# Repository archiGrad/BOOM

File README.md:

# BOOM
boom project with wannes. sensor implementatie
## includes
1: test blinkercode for 32 wroom with, but power supply is not going tgrough microusb, but through the board.  this is so we can connect the board safely to ther terminal block. in the following example i connect the VCC and GND from a 5v convertedr inbto the VIN pin and ibn tot GND pin of the nmicrocontroller though a breadboard.

<div style="display: flex; flex-wrap: wrap;">

</div>

2: screw terminal breakoput board for esp32. kiCad diagram and schamatics.
    download symbol from snapeda: https://www.snapeda.com/parts/ESP32-DEVKIT-V1/Do%20it/view-part/?t=esp32%20devkitv1

# Board Schematics
[View Schematics PDF](./media/fuse_box_schematic.pdf)

# design:
design iterations are documented here

<div style="display: flex; flex-wrap:wrap">

</div>
# partslist

https://www.automation24.be/nl/
<div style="display: flex; flex-wrap:wrap">

</div>

https://www.tinytronics.nl/

<div style="display: flex; flex-wrap:wrap">

</div>

# progressphotos
## visit 1

<div style="display: flex; flex-wrap:wrap">

</div>

### drone footage

<div style="display: flex; flex-wrap:wrap">

</div>

### print pics

<div style="display: flex; flex-wrap:wrap">

</div>

# Communication

<details>
<summary>  bespreking 1</summary>
veel kiezels, knmikkers in basin voor insecten
volgebadplaats wel 2 cm diepte nodig

oppervlakte maakt ni zoveel ui, afwatering naar allerlei andere plaatsten.

toevoegingen:
shaduw: hout, waartplant en egel compiostvat
bomen kunnen naar elkaar toegroeien, verbinding tussen elkaar

-------------------------

voor nu: waterbasin, en bloempot afmaken voor 13e
in patio, 3meter hoogte

van 3.2m tot 4m

</details>

<details><summary>  bespreking 2 </summary>
wannes:
onderkant te zwaar
meer fragiliteit
chaos particles iets j=hogert gesiuturred
animatie van gesiluleerde vectors
</details>

<details><summary>  bespreking 3 </summary>
ris, zoals ik al schreef in de groep, bedankt voor het harde werk en het tijdig afleveren van een model aan Yannick. Een fysiek schaalmodel gaat alles voor de klant veel tastbaarder maken en mij helpen in het overtuigen 🙏

Wat betreft een offerte/inschatting voor deel 2 zou ik graag een inschatting hebben voor 3 modellen en een inschatting voor 5 modellen. Graag zou ik dit zondag ontvangen

Wat betreft een korte 'groeivideo' lukt het om dit tegen maandag door te sturen ? 

Wat betreft de 'bloempot'-structuur, dit mag van mij gewoon een variatie met andere seed zijn van het huidige model, het is maar dat ik een variatie kan tonen. Graag tegen zondag (?)

Ik stuur je straks een beeld van een tuinimpressie, als je me dan 3 renders vanuit dit oogpunt ( 1x bloempot, 2x waterbassin vanuit een verschillende hoek) met een neutraal licht (liefst al met mat zwart materiaal) kan sturen  dan kan ik een impressie maken van het geheel.

Verder zie ik dat er heel wat meer werk in het geheel is gekropen, dit komt deels omdat ik je niet vanaf het begin van de volledige informatie wist te voorzien, ik vind het dan ook slechts logisch dat ik je hiervoor vergoed, ik dacht aan €1100, laat maar weten of je hiermee akkoord gaat. 

Merci!

</details>

### bespreking wannes_rens
[View PDF](./media/wannes_rens.pdf)

## inspiration:

### hacker manifesto
-[link](https://archive.org/details/pdfy-RtCf3CYEbjKrXgFe/page/n175/mode/2up)

### scematics example
-[link](https://boredomprojects.net/index.php/projects/sensors-for-hems)

### install esp32 block  on bin rail
-[link](https://www.youtube.com/watch?v=UIU_M9MApd0)

-[link](kiCad pcb layout: https://www.youtube.com/watch?v=3FGNw28xBr0)

### make an esp32 breakout block with terminal screws: -[ link](https://www.youtube.com/watch?v=nSP0rKtDYko)

### visual inspiration from pingro craters in svalbard
-[ link](https://www.researchgate.net/figure/The-pingo-and-crater-sites-A-overview-of-the-pingo-site-location-5-in-Fig-1_fig2_329979008)

<div style="display: flex; flex-wrap:wrap">

</div>

TODO:

documentje dimitri,
eerst factuur doorsturen

fase 1

plaatsinmg tov trap en plaatsing vermolmd hout 
bekabeling
enkel buitenstructuur
bekabeling, 180 graden -> 15 cm
16mm dikte druppeldarm
langs 1 poot omhhog, mag naar bionnen en buiten, plooihoek.

yannick
druppeldarm test, iun , uit, hoek, interne externe diameter
textuur test, richring verticaal nerven,
test met eilnaden

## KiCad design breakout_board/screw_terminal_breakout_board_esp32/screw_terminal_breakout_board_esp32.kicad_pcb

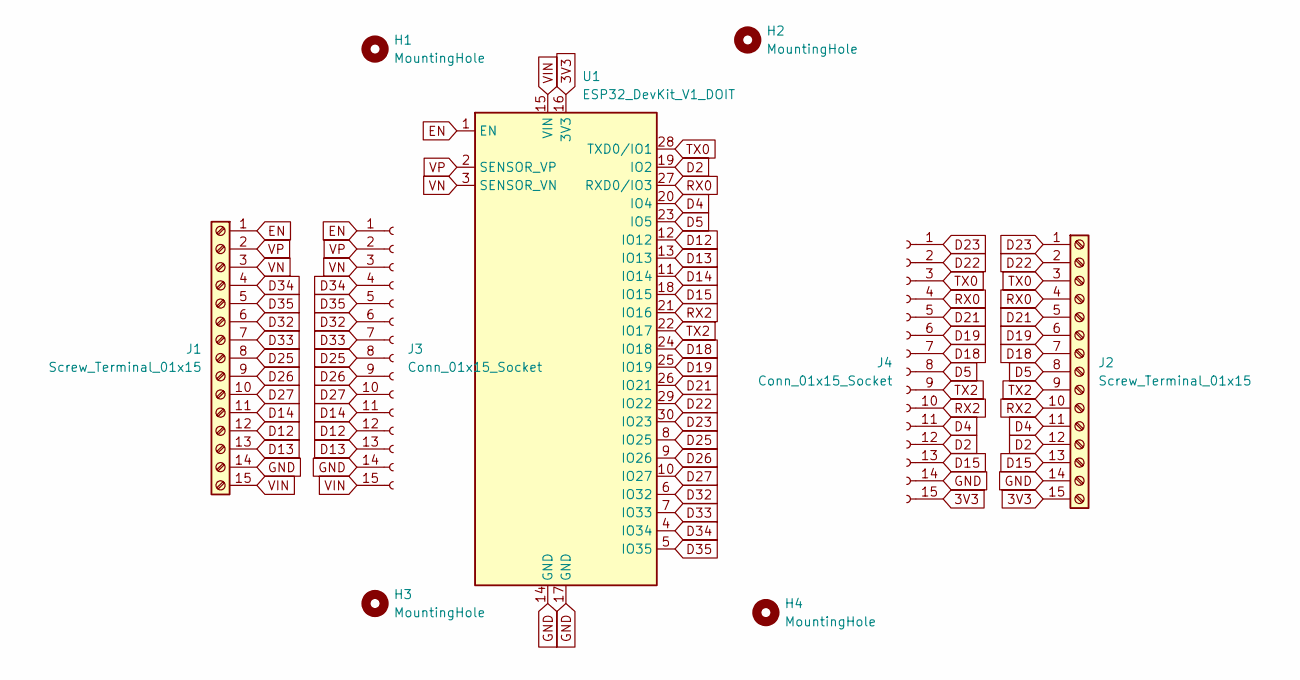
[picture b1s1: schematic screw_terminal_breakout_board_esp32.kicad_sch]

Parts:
H1, H2, H3, H4: MountingHole; MountingHole_3.2mm_M3_Pad_Via
J1, J2: Screw_Terminal_01x15; TerminalBlock_4Ucon_1x15_P3.50mm_Horizontal
J3, J4: Conn_01x15_Socket; PinHeader_1x15_P2.54mm_Vertical
U1: ESP32_DevKit_V1_DOIT; esp32_devkit_v1_doit

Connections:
3V3: J2.15, J4.15, U1.16 (3V3)
D2: J2.12, J4.12, U1.19 (IO2)
D4: J2.11, J4.11, U1.20 (IO4)
D5: J2.8, J4.8, U1.23 (IO5)
D12: J1.12, J3.12, U1.12 (IO12)
D13: J1.13, J3.13, U1.13 (IO13)
D14: J1.11, J3.11, U1.11 (IO14)
D15: J2.13, J4.13, U1.18 (IO15)
D18: J2.7, J4.7, U1.24 (IO18)
D19: J2.6, J4.6, U1.25 (IO19)
D21: J2.5, J4.5, U1.26 (IO21)
D22: J2.2, J4.2, U1.29 (IO22)
D23: J2.1, J4.1, U1.30 (IO23)
D25: J1.8, J3.8, U1.8 (IO25)
D26: J1.9, J3.9, U1.9 (IO26)
D27: J1.10, J3.10, U1.10 (IO27)
D32: J1.6, J3.6, U1.6 (IO32)
D33: J1.7, J3.7, U1.7 (IO33)
D34: J1.4, J3.4, U1.4 (IO34)
D35: J1.5, J3.5, U1.5 (IO35)
EN: J1.1, J3.1, U1.1 (EN)
GND: J1.14, J2.14, J3.14, J4.14, U1.14 (GND), U1.17 (GND)
RX0: J2.4, J4.4, U1.27 (RXD0/IO3)
RX2: J2.10, J4.10, U1.21 (IO16)
TX0: J2.3, J4.3, U1.28 (TXD0/IO1)
TX2: J2.9, J4.9, U1.22 (IO17)
VIN: J1.15, J3.15, U1.15 (VIN)
VN: J1.3, J3.3, U1.3 (SENSOR_VN)
VP: J1.2, J3.2, U1.2 (SENSOR_VP)

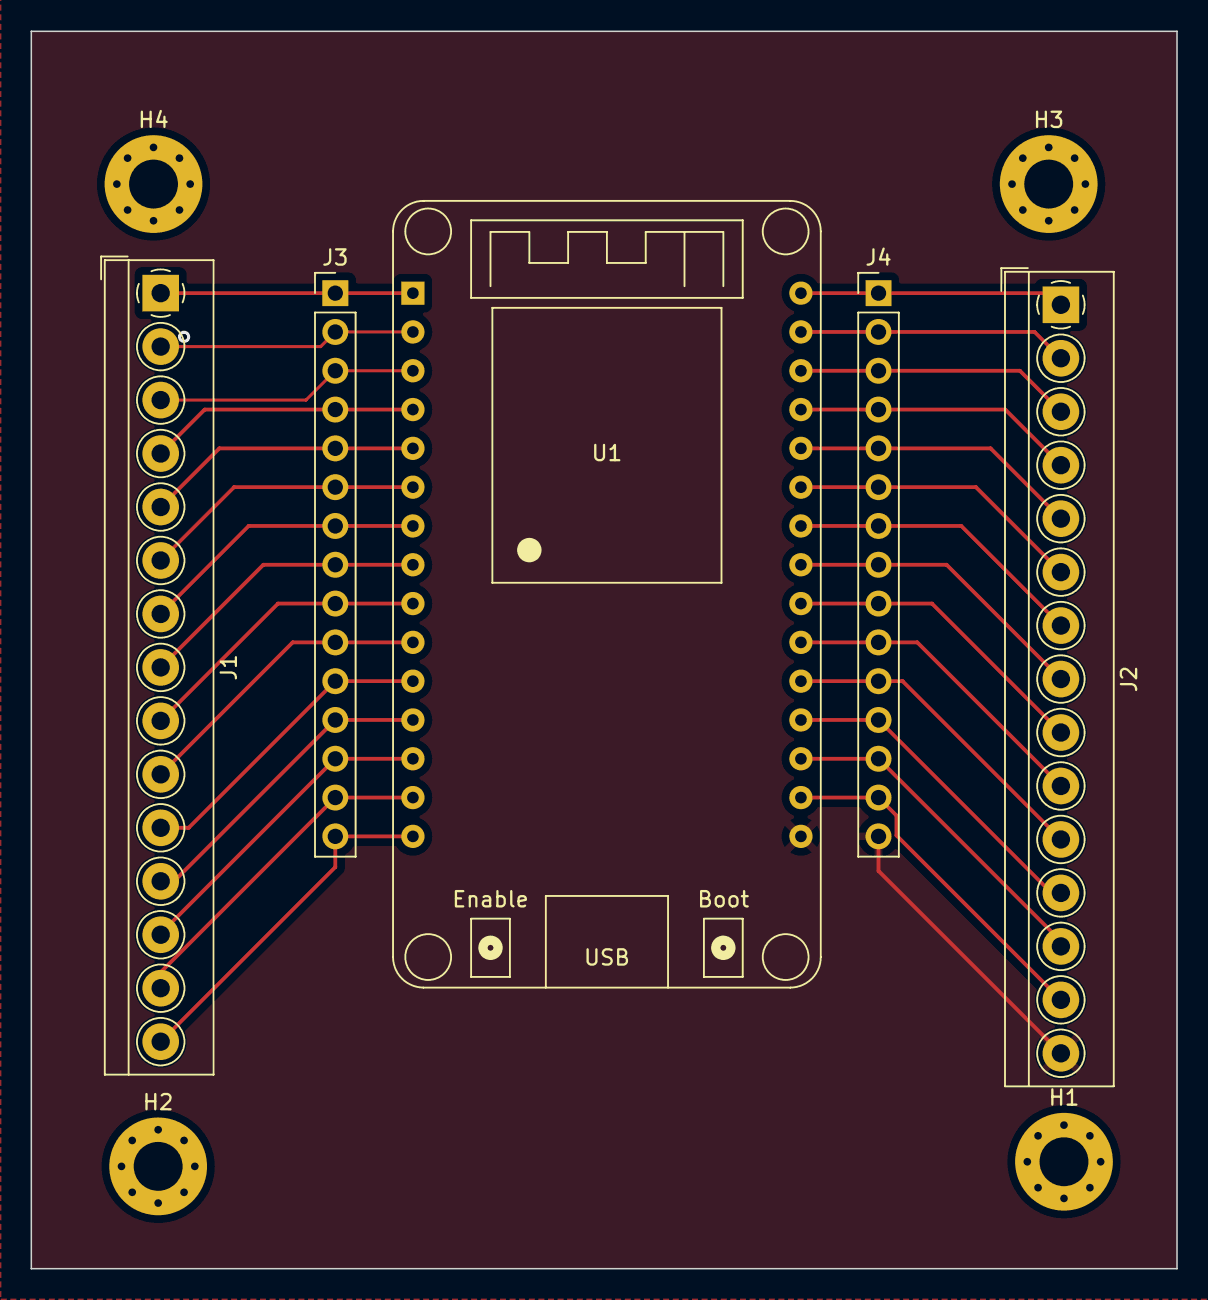
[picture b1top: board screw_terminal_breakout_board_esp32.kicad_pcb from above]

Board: 2 copper layers, 75.0 x 81.0 mm, 9 parts (0 on the bottom side), 29 nets.

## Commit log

2024-02-11 add code
2024-02-11 add media
2024-02-12 pcb update
2024-02-12 upload 1
2024-02-12 upload 2
2024-02-12 update 3
2024-02-12 update readme and media
2024-02-12 update 3d model
2024-02-12 update test 4
2024-02-14 add partslist
2024-02-19 updte pingo crater
2024-02-19 update visit 1
2024-02-27 uupdate drone fotasge
2024-02-27 udpoate
2024-07-22 screenshots 1
2024-07-22 screenshots2
2024-07-22 sdcreenshorts3
2024-07-22 screenshots4
